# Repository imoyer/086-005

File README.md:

# 086-005

Gestalt Single Stepper Node Firmware

## Introduction

This is the firware the Single Node board used in the Gestalt project by Ilan and Nadya. Which is nice. In this repository you will find files needed to program your Gestalt Single Stepper Node. You can find the files for PCB production in the [board](board) folder of this repository. Pick your revision (e.g. `rev0.4`) and make your own board!

## Installation

This repository contains [Makefile](Makefile) which is used by `make` to do the following.

1. Burn the firmware
2. Set the fuses

At the moment it is configured to use the **AVRISP mkII**. To make it work with FabISP or other AVR programmer, a lot of people will be happy if you add your custom code and make a pull request.

**First** make sure that your AVR programmer is connected. There are many ways to do it, I used `lsusb` on a MacOS system.

```
lsusb
```

The following is what I got in the list.

```
Atmel Corporation AVRISP mkII
```

Which is exactly what I need to proceed. We assume that things like `avrdude` or [CrossPack](https://www.obdev.at/products/crosspack/index.html) are already installed.

**Second**, make sure your Gestalt Node is properly connected to a power source, FTDI and AVR programmer.

At this point you can use `make` to burn the firmware.

```
make program-avrisp2
```

You should see output with things that look like progress bars and a polite **Thank you!** at the end. 

**Third** make sure that you set the fuses. For that you have to use `make` once more.

```
make program-avrisp2-fuses
```

It might ask you to reset a fuse on the way, **just hit ENTER** unless you know what you are doing.

**Congratulations!** Your Gestalt Node is ready to be used. Now go to the [pygestalt](https://github.com/nadya/pygestalt) repository and continue from there.

## Contributing

Please add anything weird to the issue tracker of this repository. If you see how you can improve things directly, submit a pull request.

Thank you!

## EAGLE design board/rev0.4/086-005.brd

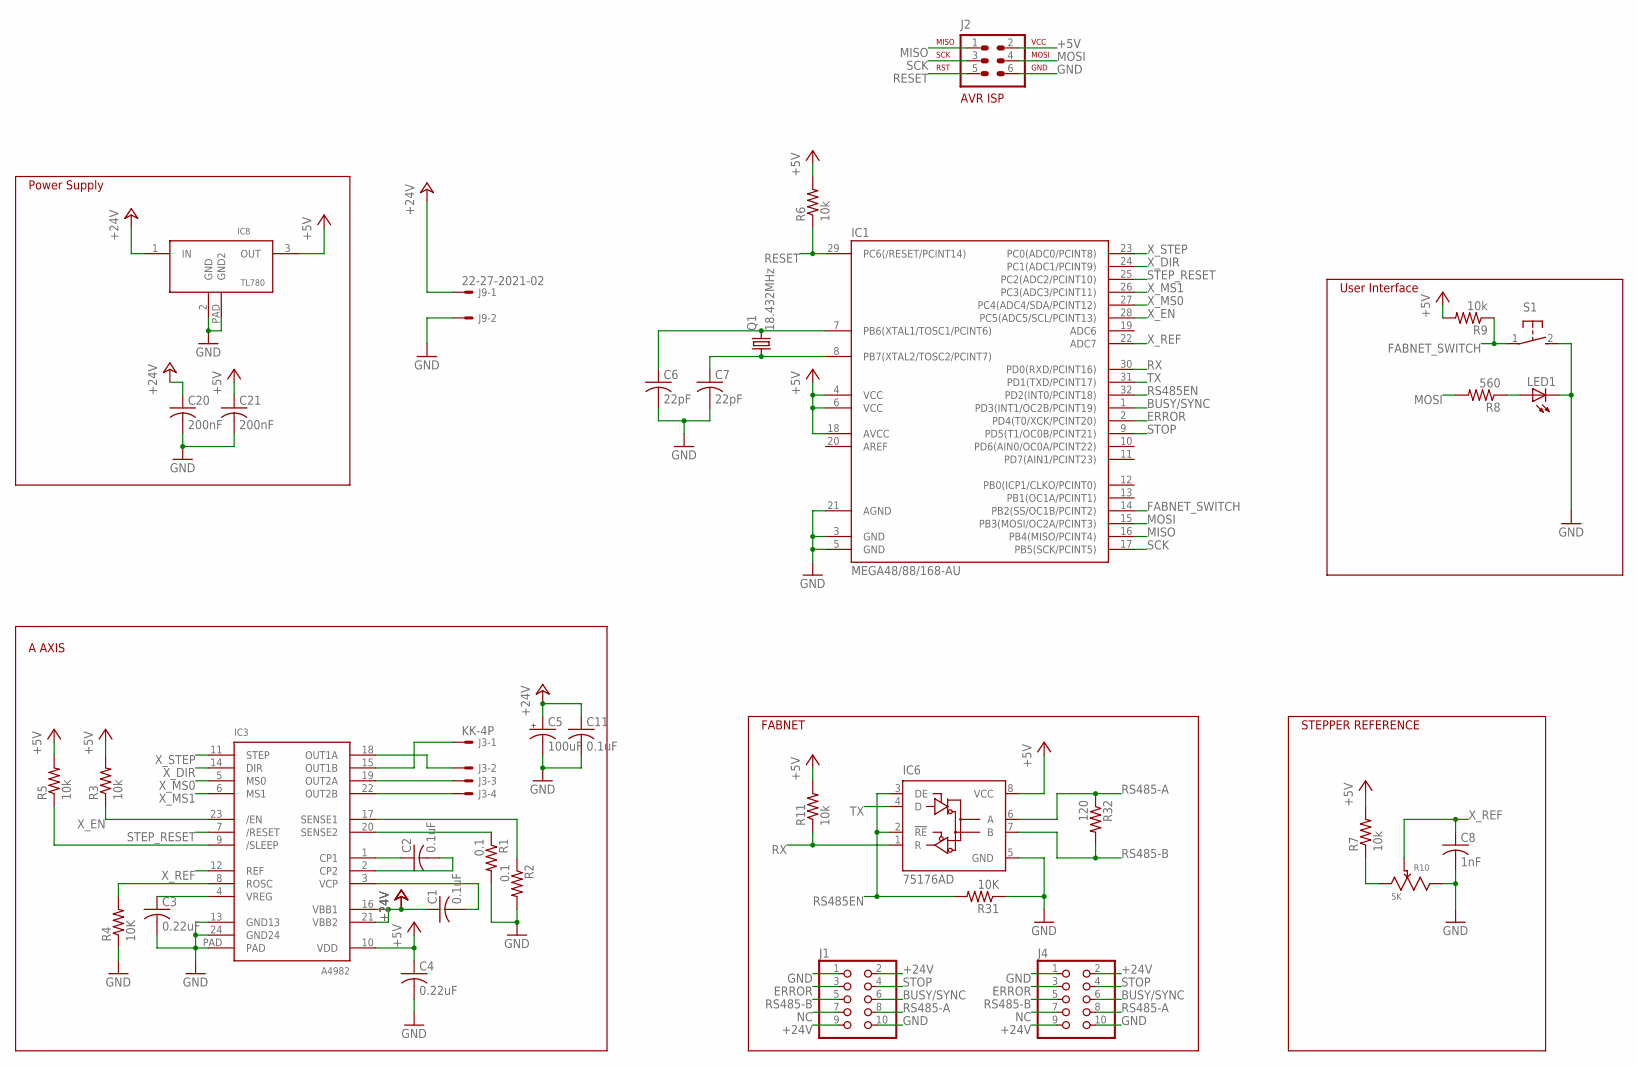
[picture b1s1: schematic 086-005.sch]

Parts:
C1, C2, C11: 0.1uF; C0805
C3, C4: 0.22uF; C0805
C5: 100uF; PANASONIC_D
C6, C7: 22pF; C0805
C8: 1nF; C0805
C20, C21: 200nF; C0805
IC1: MEGA48/88/168-AU; TQFP32-08
IC3: A4982; TSSOP24_LP
IC6: 75176AD; D_R-PDSO-G8
IC8: TL780_VREG; D2PAK-3
J1, J4: PINHD-2X5; 2X05
J2: AVR-ISP-6VERT; AVR-ISP-6
J3: KK-4P; 7395-04
J9: 22-27-2021-02; 6410-02
LED1: LEDCHIPLED_0603; CHIPLED_0603
Q1: 18.432MHz; HC49UP
R1, R2: 0.1; R1206
R3, R5, R6, R7, R9, R11: 10k; R0805
R4, R31: 10K; R0805
R8: 560; R0805
R10: 5K; BOURN_TRIM
R32: 120; R0805
S1: 31-XX; B3F-31XX

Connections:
+5V: C4.1, C21.1, IC1.4 (VCC), IC1.6 (VCC), IC1.18 (AVCC), IC3.10 (VDD), IC6.8 (VCC), IC8.3 (OUT), J2.2, R3.2, R5.2, R6.2, R7.2, R9.2, R11.2
+24V: C1.1, C5.+, C11.1, C20.1, IC3.16 (VBB1), IC3.21 (VBB2), IC8.1 (IN), J1.2, J1.9, J4.2, J4.9, J9.1
BUSY/SYNC: IC1.1 (PD3(INT1/OC2B/PCINT19)), J1.6, J4.6
ERROR: IC1.2 (PD4(T0/XCK/PCINT20)), J1.3, J4.3
FABNET_SWITCH: IC1.14 (PB2(SS/OC1B/PCINT2)), R9.1, S1.1
GND: C3.2, C4.2, C5.-, C6.2, C7.2, C8.2, C11.2, C20.2, C21.2, IC1.3 (GND), IC1.5 (GND), IC1.21 (AGND), IC3.13 (GND13), IC3.24 (GND24), IC3.PAD, IC6.5 (GND), IC8.2 (GND), IC8.PAD (GND2), J1.1, J1.10, J2.6, J4.1, J4.10, J9.2, LED1.C, R1.2, R2.2, R4.1, R10.3, R31.1, S1.2 (S)
MISO: IC1.16 (PB4(MISO/PCINT4)), J2.1
MOSI: IC1.15 (PB3(MOSI/OC2A/PCINT3)), J2.4, R8.2
N2354: R7.1, R10.1
unnamed: C6.1, IC1.7 (PB6(XTAL1/TOSC1/PCINT6)), Q1.2
unnamed: C7.1, IC1.8 (PB7(XTAL2/TOSC2/PCINT7)), Q1.1
unnamed: IC3.19 (OUT2A), J3.3
unnamed: IC3.22 (OUT2B), J3.4
unnamed: LED1.A, R8.1
unnamed: IC3.18 (OUT1A), J3.2
unnamed: IC3.15 (OUT1B), J3.1
unnamed: IC3.20 (SENSE2), R1.1
unnamed: IC3.17 (SENSE1), R2.1
unnamed: IC3.8 (ROSC), R4.2
unnamed: C1.2, IC3.3 (VCP)
unnamed: C2.1, IC3.1 (CP1)
unnamed: C2.2, IC3.2 (CP2)
unnamed: IC3.9 (/SLEEP), R5.1
unnamed: C3.1, IC3.4 (VREG)
NC: J1.7, J4.7
RESET: IC1.29 (PC6(/RESET/PCINT14)), J2.5, R6.1
RS485-A: IC6.6 (A), J1.8, J4.8, R32.1
RS485-B: IC6.7 (B), J1.5, J4.5, R32.2
RS485EN: IC1.32 (PD2(INT0/PCINT18)), IC6.2 (!RE), IC6.3 (DE), R31.2
RX: IC1.30 (PD0(RXD/PCINT16)), IC6.1 (R), R11.1
SCK: IC1.17 (PB5(SCK/PCINT5)), J2.3
STEP_RESET: IC1.25 (PC2(ADC2/PCINT10)), IC3.7 (/RESET)
STOP: IC1.9 (PD5(T1/OC0B/PCINT21)), J1.4, J4.4
TX: IC1.31 (PD1(TXD/PCINT17)), IC6.4 (D)
X_DIR: IC1.24 (PC1(ADC1/PCINT9)), IC3.14 (DIR)
X_EN: IC1.28 (PC5(ADC5/SCL/PCINT13)), IC3.23 (/EN), R3.1
X_MS0: IC1.27 (PC4(ADC4/SDA/PCINT12)), IC3.5 (MS0)
X_MS1: IC1.26 (PC3(ADC3/PCINT11)), IC3.6 (MS1)
X_REF: C8.1, IC1.22 (ADC7), IC3.12 (REF), R10.2
X_STEP: IC1.23 (PC0(ADC0/PCINT8)), IC3.11 (STEP)

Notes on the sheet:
A AXIS
Power Supply
FABNET
STEPPER REFERENCE
User Interface

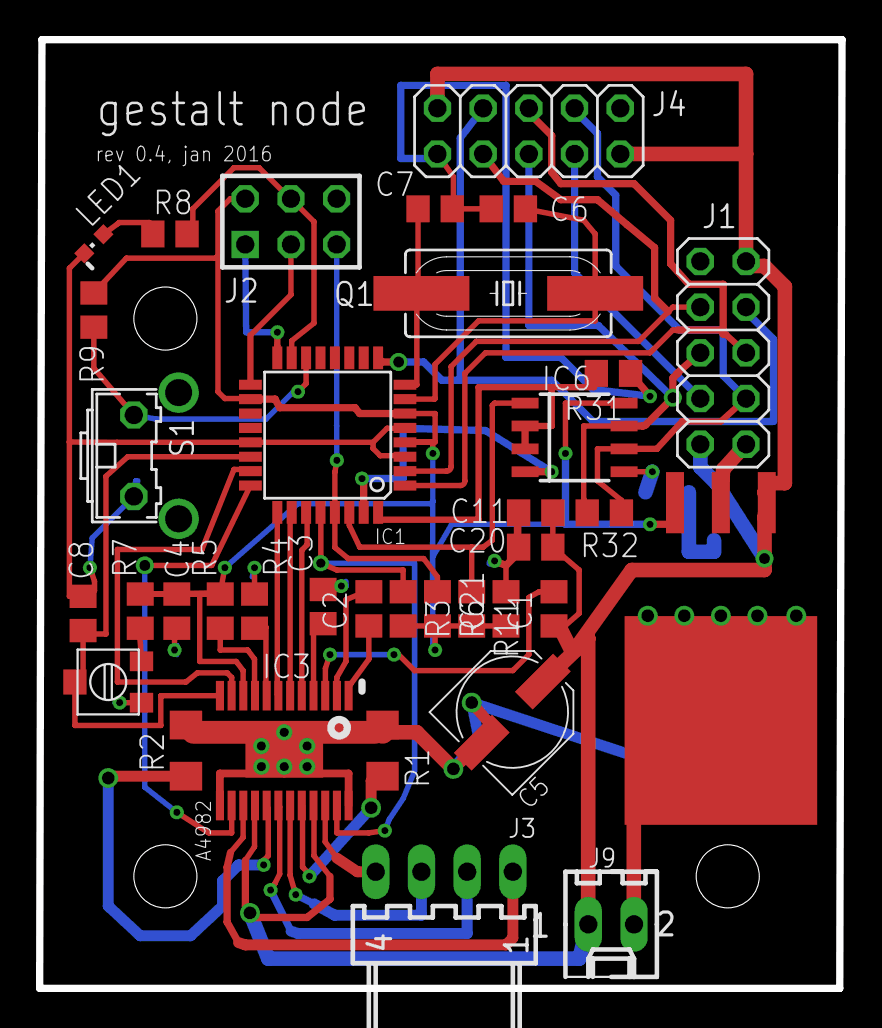
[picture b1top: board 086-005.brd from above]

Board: 2 copper layers, 44.6 x 52.7 mm, 36 parts (0 on the bottom side), 40 nets.

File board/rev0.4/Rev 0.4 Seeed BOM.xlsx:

Electronic Engineering BOM List
Product Name： Gestalt Node
Version：0.3
Issue Date：June, 2014
Item No. (序号) | Reference Des (上件位置) | Qty (用量) | Catalog (分类） | Part_Description (规格描述) | Part_Value （元件值） | Part_Package （元件封装） | Manufacturers Name (使用厂牌名称) | Manufacturers Part No. (使用厂牌型号) | Distributors Name （供应商名称） | Distributors Part No. (供貨商型号) | Unit Price （单价） | Price Break To Use （价格分段的购买量） | Notes/Remark （备注）
Example（填写范例）
1 | C1, C2, C11 | 3 | Capacitor | CAP CER 0.1UF 50V Y5V 0805 | 0.1uF | C0805
2 | C3, C4 | 2 | Capacitor | CAP CER 0.22UF 50V X7R 0805 | 0.22uF | C0805
3 | C5 | 1 | Capacitor | CAP ALUM 100UF 20% 6.3V SMD | 100uF | PANASONIC_D | Panasonic Electronic Components | EEE-0JA101SP | Digikey | PCE3852CT-ND
4 | C6, C7 | 2 | Capacitor | CAP CER 22PF 50V NP0 0805 | 22pF | C0805
5 | C8 | 1 | Capacitor | CAP CER SMD 0805 1nF 100V | 1nF | C0805
6 | C20, C21 | 2 | Capacitor | CAP CER 200nF 0805 | 200nF | C0805
7 | IC1 | 1 | IC | IC MCU 8BIT 32KB FLASH 32TQFP | MEGA48/88/168-AU | TQFP32-08 | Atmel | ATMEGA328P-ANR | Digikey | ATMEGA328P-ANRCT-ND
8 | IC3 | 1 | IC | IC MOTOR DRIVER PAR 24TSSOP | A4982 | TSSOP24_LP | Allegro MicroSystems, LLC | A4982SLPTR-T | Digikey | 620-1352-1-ND
9 | IC6 | 1 | IC | IC DIFF BUS TRANSCEIVER 8-SOIC | 75176AD | D_R-PDSO-G8 | Texas Instruments | SN75176AD | Digikey | 296-6857-5-ND
10 | IC8 | 1 | IC | IC REG LDO 5V 1.5A DDPAK | TL780_VREG | D2PAK-3 | Texas Instruments | TL780-05CKTTR | Digikey | 296-20777-1-ND
11 | J1, J4 | 2 | OTHER | 10 pin idc connector .1 inch |  | 2X05 | FCI | FCI - 95278-101A10LF | Digikey | 609-3483-6-ND
12 | J2 | 1 | OTHER | 6 pin idc connector .1 inch | AVR-ISP-6VERT | AVR-ISP-6 | FCI | FCI - 95278-101A06LF | Digikey | 609-3487-1-ND
13 | J3 | 1 | OTHER | CONN HEADER 4POS .100 R/A TIN | KK-4P | 2007100 | Molex, LLC | 22053041 | Digikey | WM4302-ND
14 | LED1 | 1 | Diode | LED BLUE CLEAR 0603 SMD |  | CHIPLED_0603
15 | Q1 | 1 | OTHER | CRYSTAL 18.432MHZ 18PF SMD | 18.432MHz | HC49UP | ECS Inc | ECS-184-18-5PX-TR | Digikey | XC1285CT-ND
16 | R1, R2 | 2 | Resister | RES SMD 0.1 OHM 5% 1W 1206 | 0.1 | R1206
17 | R3, R4, R5, R6, R7, R9, R11, R31 | 8 | Resister | RES SMD 10K OHM 1% 1/8W 0805 | 10k | R0805
18 | R8 | 1 | Resister | RES SMD 560 OHM 5% 1/8W 0805 | 560 | R0805
19 | R10 | 1 | Resister | TRIMMER 5K OHM 0.25W SMD | 5K | BOURN_TRIM | Murata Electronics North America | PVG3G502C01R00 | Digikey | 490-6996-1-ND
20 | R32 | 1 | Resister | RES SMD 120 OHM 5% 1/8W 0805 | 120 | R0805
21 | S1 | 1 | OTHER | SWITCH TACTILE SPST-NO 0.05A 24V |  | B3F-31XX | Omron Electronics Inc-EMC Div | B3F-3152 | Digikey | SW410-ND
1. Recommended Distributor: Digi-Key, Mouser, Avnet Express, Farnell.
2. Catalog: Capacitor,Resister,Diode,Connector,Transistor,IC,PROTECTOR CATEGORY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
3. Required Fields: Item No, Reference Des, Qty, Catalog, Part_Value, Part Pack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
Optional Fields: Part_Description, Manufacturers Name, Manufacturers Part No, D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

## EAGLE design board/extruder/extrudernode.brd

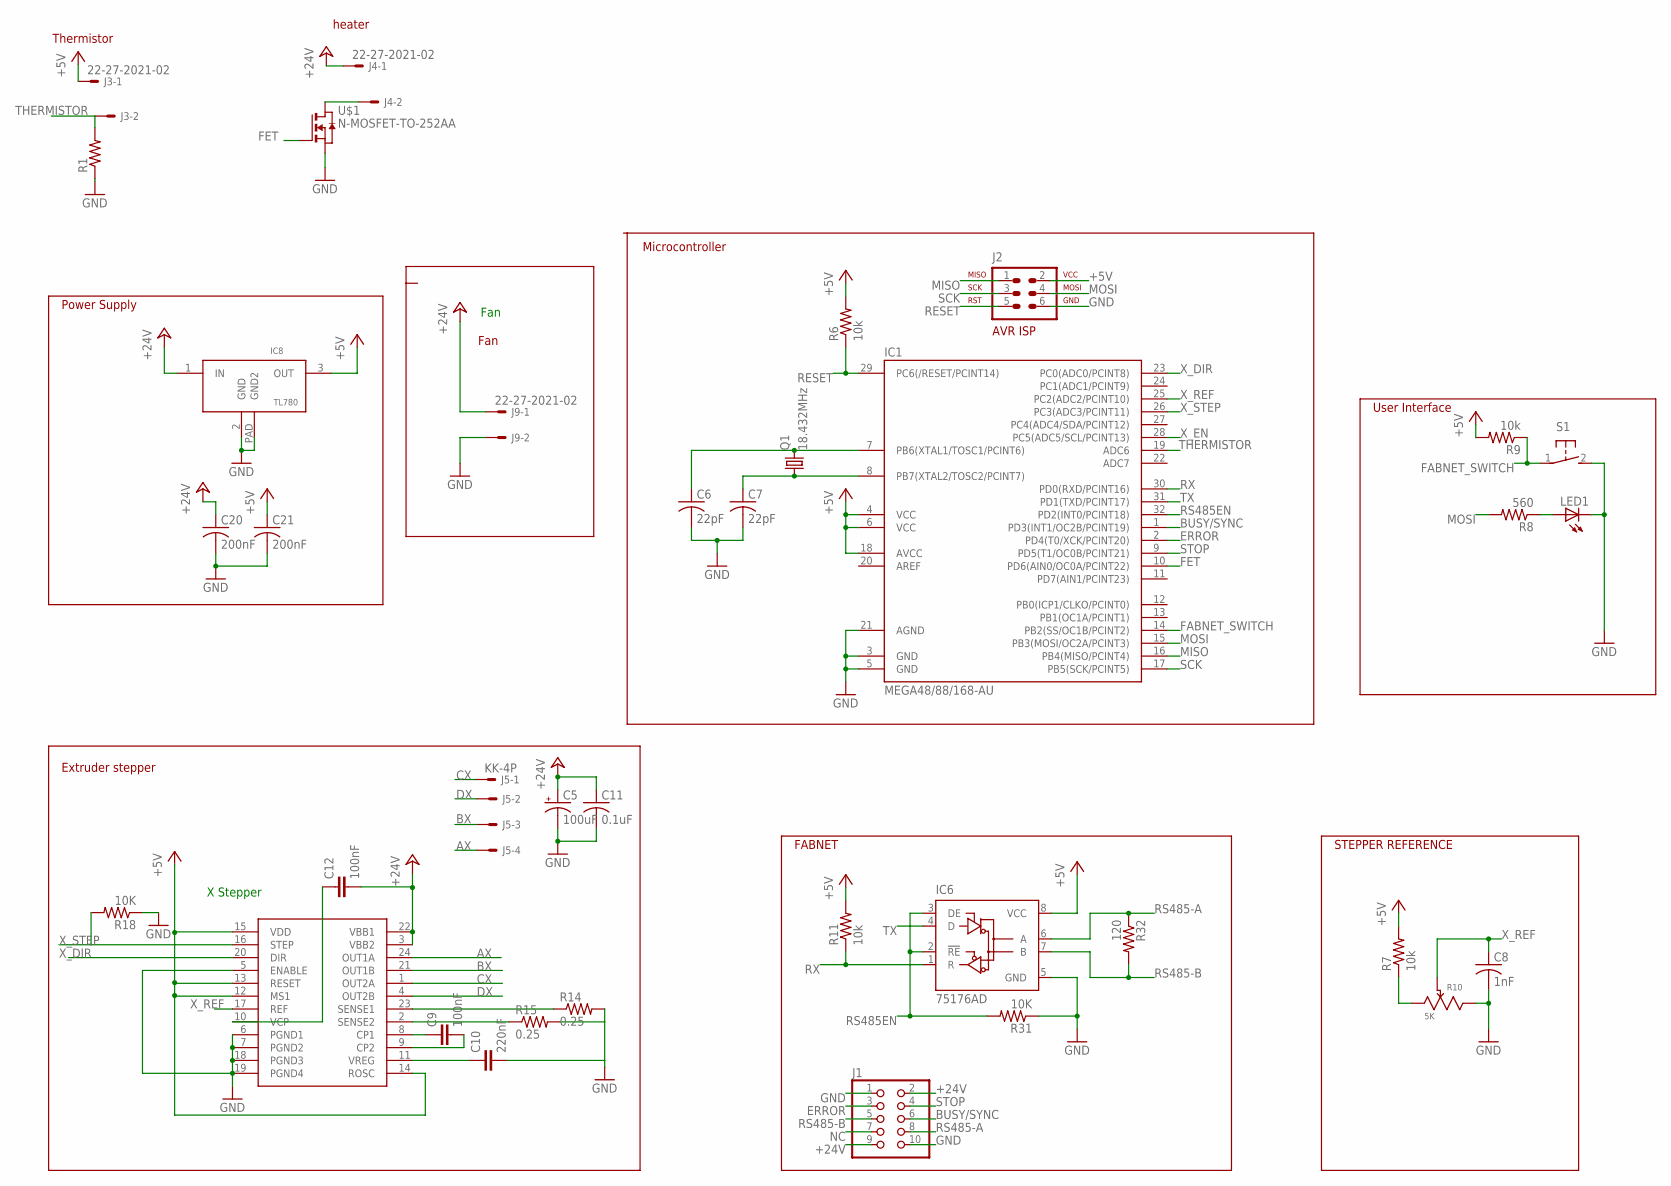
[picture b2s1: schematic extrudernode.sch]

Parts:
C5: 100uF; PANASONIC_D
C6, C7: 22pF; C0805@1
C8: 1nF; C0805@1
C9, C12: 100nF; C1206
C10: 220nF; C1206
C11: 0.1uF; C0805@1
C20, C21: 200nF; C0805@1
DRIVER3: A3982; SO24W
IC1: MEGA48/88/168-AU; TQFP32-08
IC6: 75176AD; D_R-PDSO-G8
IC8: TL780_VREG; D2PAK-3
J1: PINHD-2X5; 2X05
J2: AVR-ISP-6VERT; AVR-ISP-6
J3, J4, J9: 22-27-2021-02; 6410-02
J5: KK-4P; 7395-04
LED1: LEDCHIPLED_0603; CHIPLED_0603
Q1: 18.432MHz; HC49UP
R1: RESISTOR1206; 1206
R6, R7, R9, R11: 10k; R0805
R8: 560; R0805
R10: 5K; BOURN_TRIM
R14, R15: 0.25; R2512
R18: 10K; R1206
R31: 10K; R0805
R32: 120; R0805
S1: 31-XX; B3F-31XX
U$1: N-MOSFET-TO-252AA; TO-252AA

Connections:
+5V: C21.1, DRIVER3.12 (MS1), DRIVER3.13 (RESET), DRIVER3.14 (ROSC), DRIVER3.15 (VDD), IC1.4 (VCC), IC1.6 (VCC), IC1.18 (AVCC), IC6.8 (VCC), IC8.3 (OUT), J2.2, J3.1, R6.2, R7.2, R9.2, R11.2
+24V: C5.+, C11.1, C12.2, C20.1, DRIVER3.3 (VBB2), DRIVER3.22 (VBB1), IC8.1 (IN), J1.2, J1.9, J4.1, J9.1
AX: DRIVER3.24 (OUT1A), J5.4
BUSY/SYNC: IC1.1 (PD3(INT1/OC2B/PCINT19)), J1.6
BX: DRIVER3.21 (OUT1B), J5.3
CX: DRIVER3.1 (OUT2A), J5.1
DX: DRIVER3.4 (OUT2B), J5.2
ERROR: IC1.2 (PD4(T0/XCK/PCINT20)), J1.3
FABNET_SWITCH: IC1.14 (PB2(SS/OC1B/PCINT2)), R9.1, S1.1
FET: IC1.10 (PD6(AIN0/OC0A/PCINT22)), U$1.GATE (G)
GND: C5.-, C6.2, C7.2, C8.2, C10.2, C11.2, C20.2, C21.2, DRIVER3.5 (ENABLE), DRIVER3.6 (PGND1), DRIVER3.7 (PGND2), DRIVER3.18 (PGND3), DRIVER3.19 (PGND4), IC1.3 (GND), IC1.5 (GND), IC1.21 (AGND), IC6.5 (GND), IC8.2 (GND), IC8.PAD (GND2), J1.1, J1.10, J2.6, J9.2, LED1.C, R1.1, R10.3, R14.2, R15.2, R18.1, R31.1, S1.2 (S), U$1.SOURCE (S)
MISO: IC1.16 (PB4(MISO/PCINT4)), J2.1
MOSI: IC1.15 (PB3(MOSI/OC2A/PCINT3)), J2.4, R8.2
N2354: R7.1, R10.1
unnamed: C6.1, IC1.7 (PB6(XTAL1/TOSC1/PCINT6)), Q1.2
unnamed: C7.1, IC1.8 (PB7(XTAL2/TOSC2/PCINT7)), Q1.1
unnamed: LED1.A, R8.1
unnamed: J4.2, U$1.DRAIN (D)
unnamed: DRIVER3.23 (SENSE1), R14.1
unnamed: DRIVER3.2 (SENSE2), R15.1
unnamed: C9.1, DRIVER3.8 (CP1)
unnamed: C9.2, DRIVER3.9 (CP2)
unnamed: C10.1, DRIVER3.11 (VREG)
unnamed: C12.1, DRIVER3.10 (VCP)
NC: J1.7
RESET: IC1.29 (PC6(/RESET/PCINT14)), J2.5, R6.1
RS485-A: IC6.6 (A), J1.8, R32.1
RS485-B: IC6.7 (B), J1.5, R32.2
RS485EN: IC1.32 (PD2(INT0/PCINT18)), IC6.2 (!RE), IC6.3 (DE), R31.2
RX: IC1.30 (PD0(RXD/PCINT16)), IC6.1 (R), R11.1
SCK: IC1.17 (PB5(SCK/PCINT5)), J2.3
STOP: IC1.9 (PD5(T1/OC0B/PCINT21)), J1.4
THERMISTOR: IC1.19 (ADC6), J3.2, R1.2
TX: IC1.31 (PD1(TXD/PCINT17)), IC6.4 (D)
X_DIR: DRIVER3.20 (DIR), IC1.23 (PC0(ADC0/PCINT8))
X_EN: IC1.28 (PC5(ADC5/SCL/PCINT13))
X_REF: C8.1, DRIVER3.17 (REF), IC1.25 (PC2(ADC2/PCINT10)), R10.2
X_STEP: DRIVER3.16 (STEP), IC1.26 (PC3(ADC3/PCINT11)), R18.2

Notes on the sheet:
Extruder stepper
Power Supply
FABNET
STEPPER REFERENCE
User Interface
X Stepper
Fan
Thermistor
heater
Microcontroller

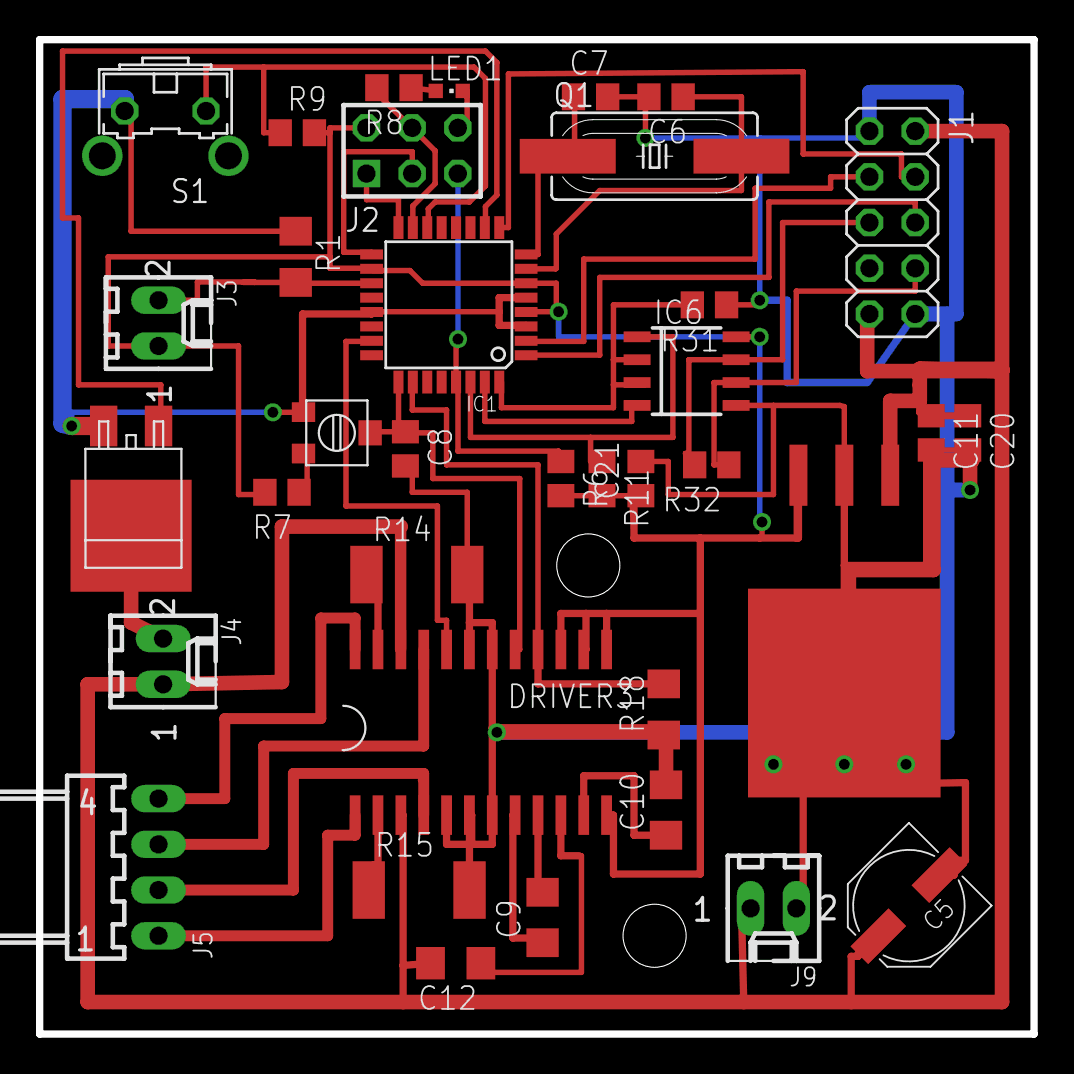
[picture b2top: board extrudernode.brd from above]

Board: 2 copper layers, 55.2 x 55.2 mm, 36 parts (0 on the bottom side), 36 nets.

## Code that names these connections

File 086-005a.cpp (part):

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#define motorPORT   PORTC
#define motorDDR    DDRC
#define motorPIN    PINC
#define motorStep   PC0
#define motorDir    PC1
#define motorReset  PC2
#define motorMS1    PC3
#define motorMS0    PC4
#define motorEnable PC5
//Motor Current REF is on ADC7


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const uint8_t setVelocityPort     = 24; //sets current velocity
const uint8_t spinStatusPort      = 26; //get spin status

const uint8_t syncPort            = 30; //triggers a sync. This is a soft proxy for the sync control line.

//Move Packet Definition
#define moveMajorSteps  0
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volatile uint8_t readPosition = 0; //gets incremented and then read, so reflects location that was last read
volatile uint8_t writePosition = 0; //gets incremented and then written, so reflects location that was last written to.
volatile uint8_t segmentKeyCounter = 255; //used to pull new segment keys. The counter is incremented, and then a key is pulled.
volatile uint8_t syncSearchPosition = 0; //the last buffer location where a search for a sync packet has been conducted.


//DIRECTION MASKS
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volatile uint32_t uVelocity = 0;
volatile uint32_t uPosition = 0;  //uSteps
const uint32_t uSteps = 1048576;  //uSteps per step (2^20)
volatile uint8_t waitingForSync = 0;  //this will get set to 1 when the move interrupt is waiting on a sync.
volatile uint8_t antiLockout = 0; //if 1, indicates that velocity should be returned to zero at end of move.


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      }

        if(moveBuffer[readPosition + 1].waitForSync == 0){
          waitingForSync = 0;  //indicate to external processes that not waiting for sync.
          *IO_ledPORT &= ~IO_ledPin; //REMOVE turn off led
          // ENABLE AXES
          enableDriver();
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
void svcSync(){
  if(waitingForSync){
    TCNT1 = 0;  //clear counter to synchronize clocks off of sync move.
  } //this also gives 921 clock cycles to complete this routine.
  uint8_t newSyncSearchPosition = syncSearchPosition;

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
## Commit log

2013-03-14 added user loop
2013-09-03 as used in thesis
2013-10-15 added cable doc image
2013-10-15 moved some of the board files to their own directory, added the board revision with the mounting holes.
2013-10-15 made a history folder to contain old makefile versions and other stuff we're not using
2013-10-15 removed .pyc files from version control
2013-10-18 added avrisp rules to makefile
2013-10-18 fixed bug with compiling bootloader in makefile
2013-10-18 added the fabnet adapter from mtm.cba.mit.edu/fabinabox/dev/fabnet/overview.html
2014-05-02 added new board version with extra connector so you don't have to cable through.
2014-06-22 added an extra connector so you can use multiple cables for connecting
2014-12-03 added BOM for latest board rev (0.3)
2014-12-12 added a new node for 3d printing heads with connectors for a thermistor, heater wire, and a stepper motor for extrusion of filament. software to follow
2014-12-12 added updated milling files for modela
2014-12-15 added board outline for extruder node
2014-12-15 updated extruder traces with some milling mistake fixes
2015-05-22 made sure makefile was in application mode
2015-11-06 added board outline for fabnet adapter
2016-05-04 changed problematic capacitor in the bom to be 50v not 6.3v
2016-07-07 added a new version for seeed requirement
2016-07-08 oops wrong BOM
2018-05-11 Add basic instructions to README.md
2018-05-13 added usbtiny to makefile
2019-03-04 Fix SeeedStudio BOM
2019-11-14 Add an image for easier part placement
2019-11-14 Add version number to part placement image
2019-11-22 Add solderpaste gerber for Seeed SMT stencil
2020-01-25 Added license file
